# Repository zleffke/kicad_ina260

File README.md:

# kicad_ina260
INA260 Current Sensor breakout board in KiCad

### Version 1
Simple breakout with I2C interface and emergency output disable features.

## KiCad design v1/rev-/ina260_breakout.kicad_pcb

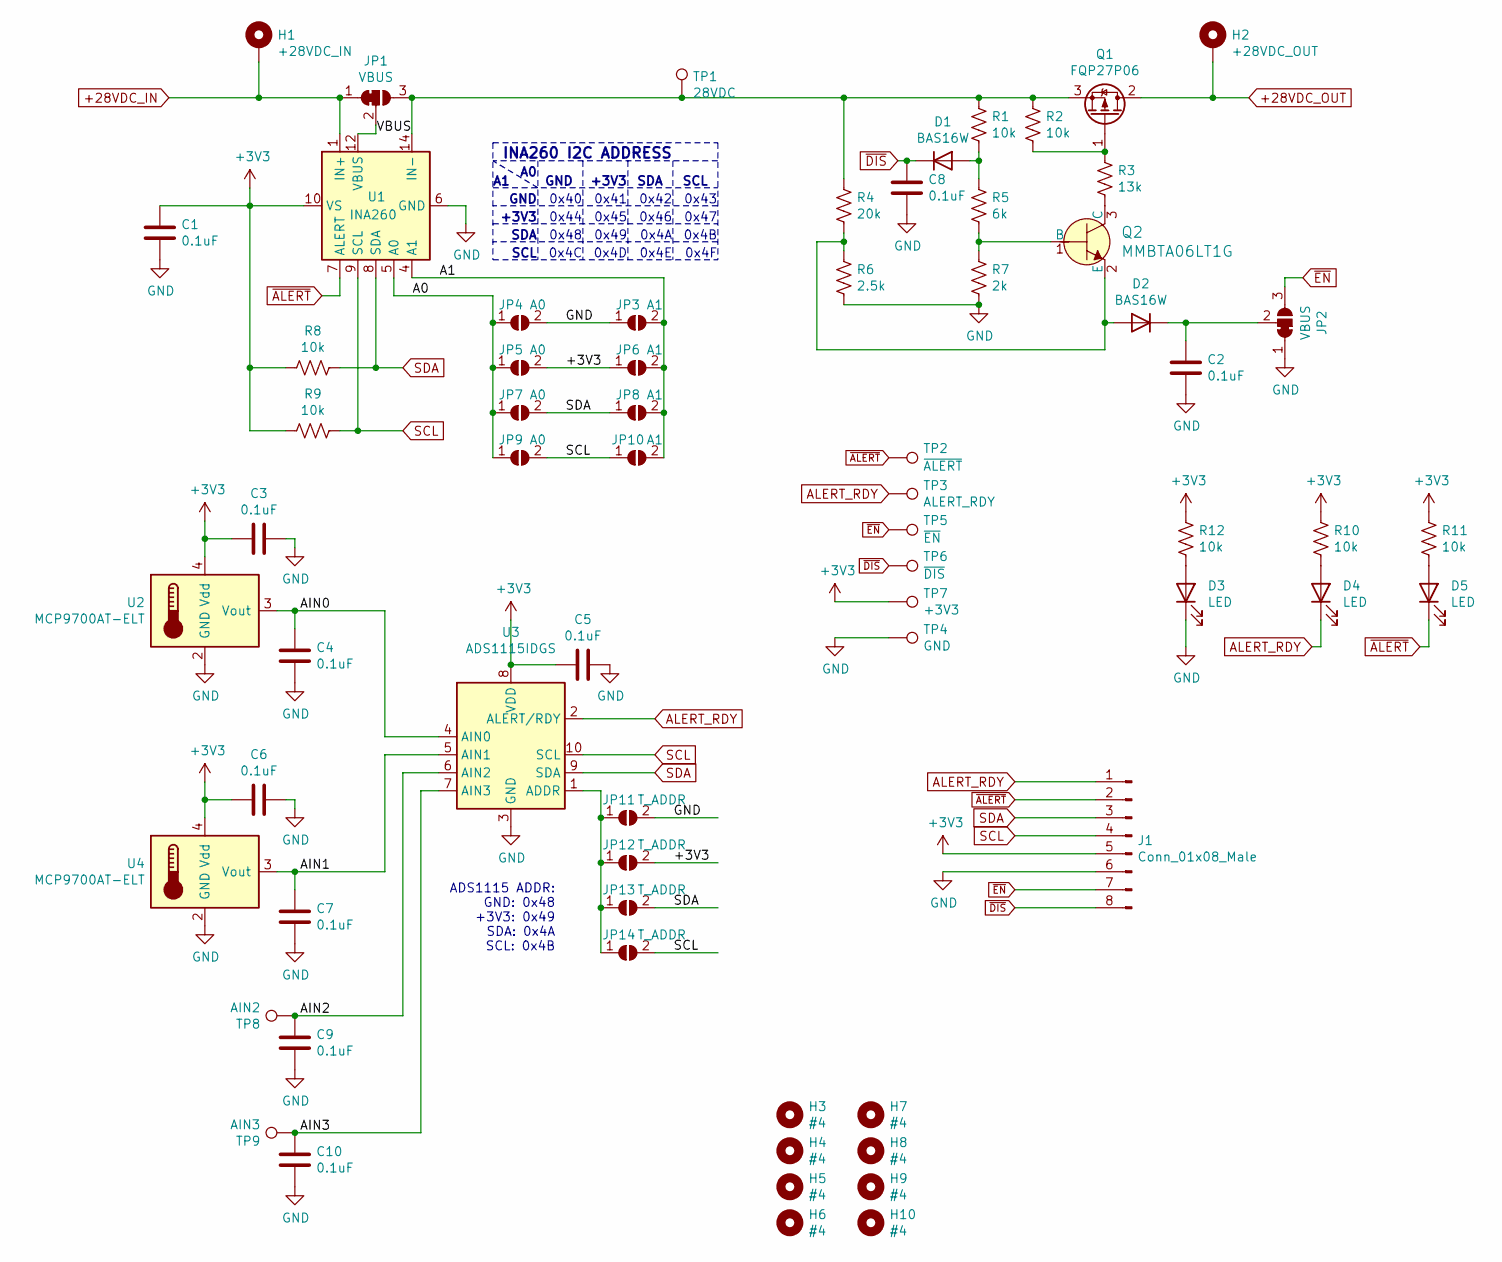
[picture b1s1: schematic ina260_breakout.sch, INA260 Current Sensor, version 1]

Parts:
C1, C2, C3, C4, C5, C6, C7, C8, C9, C10: 0.1uF; 0805
D1, D2: BAS16W; SOT-323_SC-70
D3, D4, D5: LED; LED_0805_2012Metric
H1: +28VDC_IN; MountingHole_3.7mm_Pad_Via
H2: +28VDC_OUT; MountingHole_3.7mm_Pad_Via
H3, H4, H5, H6, H7, H8, H9, H10: #4; MountingHole_3.2mm_M3
J1: Conn_01x08_Male; PinHeader_1x08_P2.54mm_Vertical
JP1, JP2: VBUS; SolderJumper-3_P1.3mm_Bridged12_RoundedPad1.0x1.5mm
JP3, JP6, JP8, JP10: A1; SolderJumper-2_P1.3mm_Open_RoundedPad1.0x1.5mm
JP4, JP5, JP7, JP9: A0; SolderJumper-2_P1.3mm_Open_RoundedPad1.0x1.5mm
JP11, JP12, JP13, JP14: T_ADDR; SolderJumper-2_P1.3mm_Open_RoundedPad1.0x1.5mm
Q1: FQP27P06; TO-263-2
Q2: MMBTA06LT1G; SOT-23-3; MPN MMBTA06LT1G; Digi-Key_PN MMBTA06LT1GOSCT-ND
R1, R2, R8, R9, R10, R11, R12: 10k; 0805
R3: 13k; 0805
R4: 20k; 0805
R5: 6k; 0805
R6: 2.5k; 0805
R7: 2k; 0805
TP1: 28VDC; TestPoint_Pad_4.0x4.0mm
TP2: ~ALERT; TestPoint_Pad_2.5x2.5mm
TP3: ALERT_RDY; TestPoint_Pad_2.5x2.5mm
TP4: GND; TestPoint_Pad_2.5x2.5mm
TP5: ~EN; TestPoint_Pad_2.5x2.5mm
TP6: ~DIS; TestPoint_Pad_2.5x2.5mm
TP7: +3V3; TestPoint_Pad_2.5x2.5mm
TP8: AIN2; TestPoint_Pad_2.5x2.5mm
TP9: AIN3; TestPoint_Pad_2.5x2.5mm
U1: INA260; TSSOP-16_4.4x5mm_P0.65mm
U2, U4: MCP9700AT-ELT; SOT-353_SC-70-5
U3: ADS1115IDGS; TSSOP-10_3x3mm_P0.5mm

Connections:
+3V3: C1.1, C3.2, C5.2, C6.2, J1.5, JP5.2 (B), JP6.1 (A), JP12.2 (B), R8.2, R9.2, R10.2, R11.2, R12.2, TP7.1, U1.10 (VS), U2.4 (Vdd), U3.8 (VDD), U4.4 (Vdd)
+28VDC_IN: H1.1, JP1.1 (A), U1.1 (IN+), U1.2 (IN+), U1.3 (IN+)
+28VDC_OUT: H2.1, Q1.2 (D)
/A0: JP4.1 (A), JP5.1 (A), JP7.1 (A), JP9.1 (A), U1.5 (A0)
/A1: JP3.2 (B), JP6.2 (B), JP8.2 (B), JP10.2 (B), U1.4 (A1)
/AIN0: C4.1, U2.3 (Vout), U3.4 (AIN0)
/AIN1: C7.1, U3.5 (AIN1), U4.3 (Vout)
/AIN2: C9.1, TP8.1, U3.6 (AIN2)
/AIN3: C10.1, TP9.1, U3.7 (AIN3)
/VBUS: JP1.2 (C), U1.12 (VBUS)
ALERT_RDY: D4.1 (K), J1.1, TP3.1, U3.2 (ALERT/RDY)
GND: C1.2, C2.2, C3.1, C4.2, C5.1, C6.1, C7.2, C8.2, C9.2, C10.2, D3.1 (K), J1.6, JP2.1 (A), JP3.1 (A), JP4.2 (B), JP11.2 (B), R6.2, R7.2, TP4.1, U1.6 (GND), U1.11 (GND), U2.2 (GND), U3.3 (GND), U4.2 (GND)
unnamed: C2.1, D2.3 (K), JP2.2 (C)
unnamed: D1.1 (A), R1.2, R5.1
unnamed: D2.1 (A), Q2.2 (E), R4.2, R6.1
unnamed: D3.2 (A), R12.1
unnamed: D4.2 (A), R10.1
unnamed: D5.2 (A), R11.1
unnamed: JP1.3 (B), Q1.3 (S), R1.1, R2.1, R4.1, TP1.1, U1.14 (IN-), U1.15 (IN-), U1.16 (IN-)
unnamed: JP11.1 (A), JP12.1 (A), JP13.1 (A), JP14.1 (A), U3.1 (ADDR)
unnamed: Q1.1 (G), R2.2, R3.1
unnamed: Q2.1 (B), R5.2, R7.1
unnamed: Q2.3 (C), R3.2
SCL: J1.4, JP9.2 (B), JP10.1 (A), JP14.2 (B), R9.1, U1.9 (SCL), U3.10 (SCL)
SDA: J1.3, JP7.2 (B), JP8.1 (A), JP13.2 (B), R8.1, U1.8 (SDA), U3.9 (SDA)
~ALERT: D5.1 (K), J1.2, TP2.1, U1.7 (ALERT)
~DIS: C8.1, D1.3 (K), J1.8, TP6.1
~EN: J1.7, JP2.3 (B), TP5.1

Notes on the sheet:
ADS1115 ADDR: GND: 0x48 +3V3: 0x49 SDA: 0x4A SCL: 0x4B
GND
SCL
SDA
+3V3
0x40
0x41
0x43
0x44
0x45
0x46
0x47
0x48
0x4C
0x49
0x4D
0x4A
0x4E
0x4F
0x4B
0x42
INA260 I2C ADDRESS

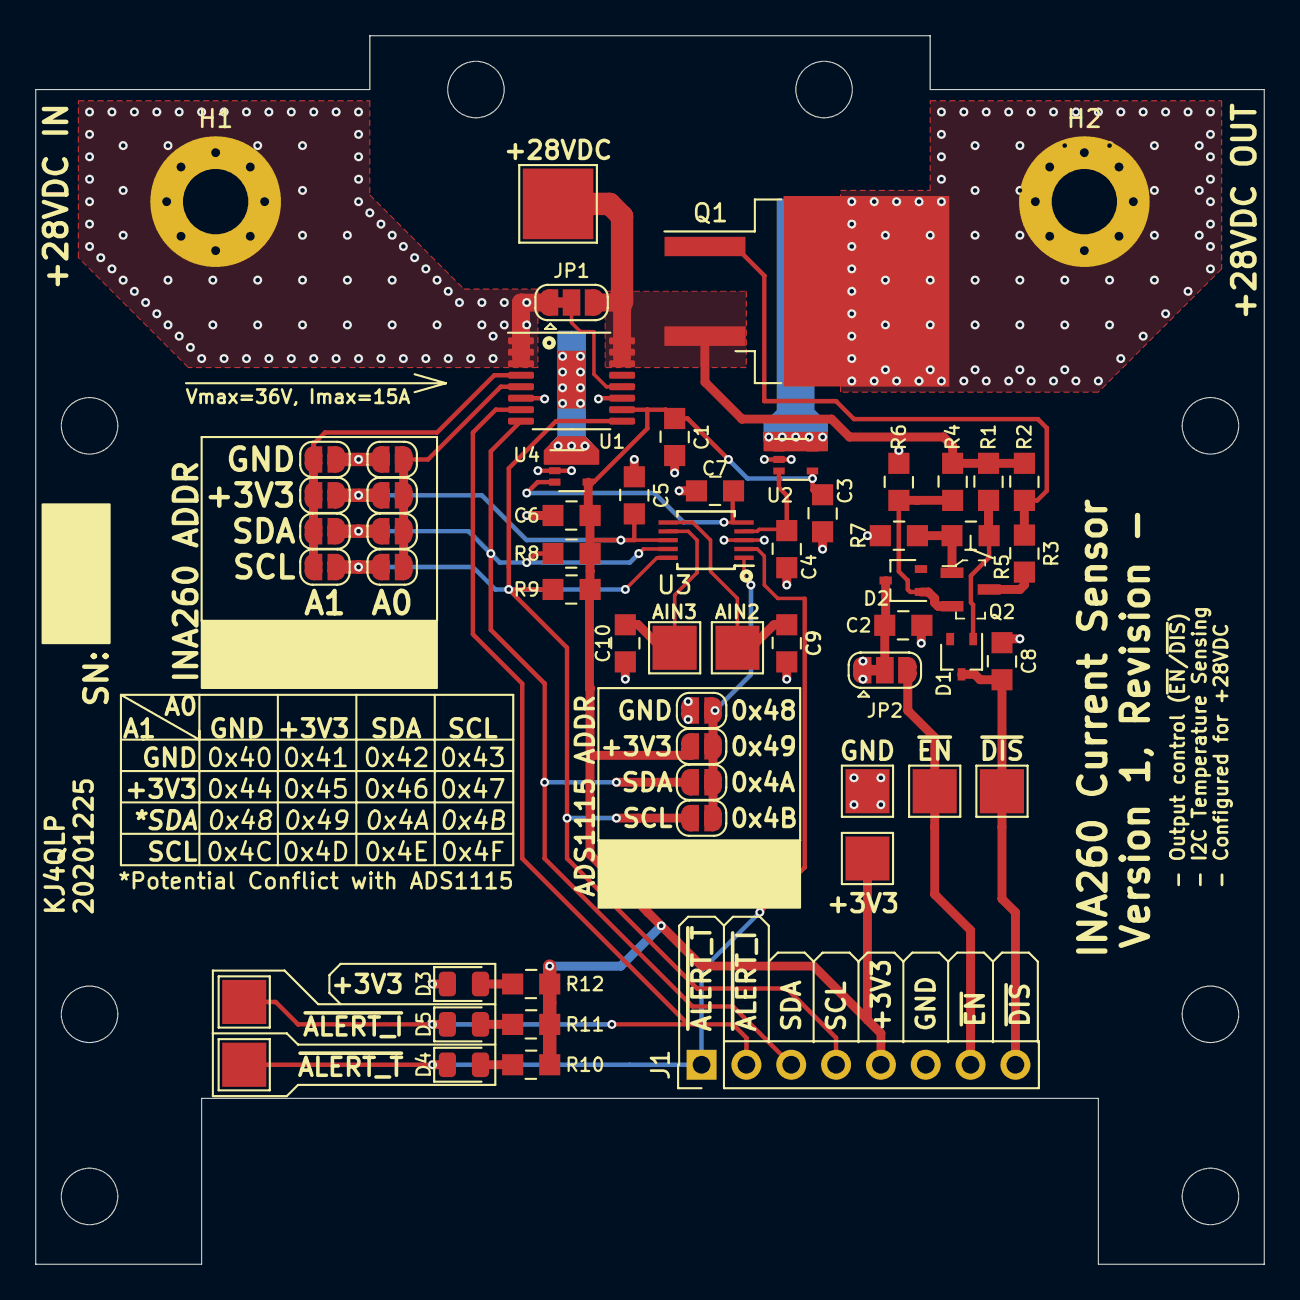
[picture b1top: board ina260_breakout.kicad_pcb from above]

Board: 2 copper layers, 69.6 x 69.6 mm, 67 parts (0 on the bottom side), 28 nets.

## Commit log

2020-12-25 commit of V1 - breakout board with temp sense and output control. This commit submitted to osh park on 20201225.

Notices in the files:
v1/rev-/ina260_breakout.sch:
creativecommons.org/licenses/by/4.0
License: CC BY 4.0
